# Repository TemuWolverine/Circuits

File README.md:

# Circuits

A collection of PCB designs & KiCad parts that aren't part of larger projects.

### [KicadCustomParts](https://github.com/TemuWolverine/Circuits/tree/master/KicadCustomParts)
- ESP32-S3-Supermini 
    * footprint
    * symbol

### [SparkleButton](https://github.com/TemuWolverine/Circuits/tree/master/SparkleBoard)
Designed as a WS2812b/"Neopixel" push button. Uses two (linked) tactile momentary switches and a WS2812b pixel. The idea is some push buttons can also act as status lights - think the power button on a console - but most off the shelf push buttons are a fixed LED colour.

Needs 5v (LED), LED signal, switch signal and GND.

3D enclosure to come soon.

### [SparkleBoard](https://github.com/TemuWolverine/Circuits/tree/master/SparkleButton)

WIP, USB-PD decoy/trigger and buck converter to provide two voltages. ie 12v for various parts of a project, and 5v for MCU.

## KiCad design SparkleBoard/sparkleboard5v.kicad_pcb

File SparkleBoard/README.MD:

# SparkleBoard 5v (WIP)
SparkleBoard is a USB-PD power board that provides two power rails - one is user selectable from 12v, 15v, 18v or 20v (if the USB-PD power brick supports it) by using jumpers. The other power rail is 5v for microcontrollers.

Amperage defaults to 2a, can be set to 3.25a by cutting JP1

## 5v  -> 3.3v
5v rail is provided via a buck converter - [AP63205](https://www.diodes.com/part/view/AP63205), an inexpensive fixed voltage buck converter from Diodes.

If you wanted 3.3v, this could be achieved by swapping out the chip for the AP63203, and changing the inductor to 3.9uH (from 4.7uH). The rest of the circuit design remains the same according to the manufacturer.

> Note: the AP63200/AP63201 are not fixed voltage output IC's and require additional circuitry with different values and are **NOT** drop in replacements.

## Datasheets
* [AP63205](https://www.diodes.com/datasheet/download/AP63200-AP63201-AP63203-AP63205.pdf)
* [HUSB238](https://www.hynetek.com/uploadfiles/site/219/news/aabbbbdb-48c9-4a44-a6dc-2c15f53282e6.pdf)

## References
* [Sparkfun Babybuck](https://github.com/sparkfun/Buck_Regulator_AP63203/tree/main) (AP6320***3***)
* [Adafruit HUSB238 breakout board](https://github.com/adafruit/Adafruit-USB-Type-C-Power-Delivery-Dummy-Breakout-PCB/tree/main)

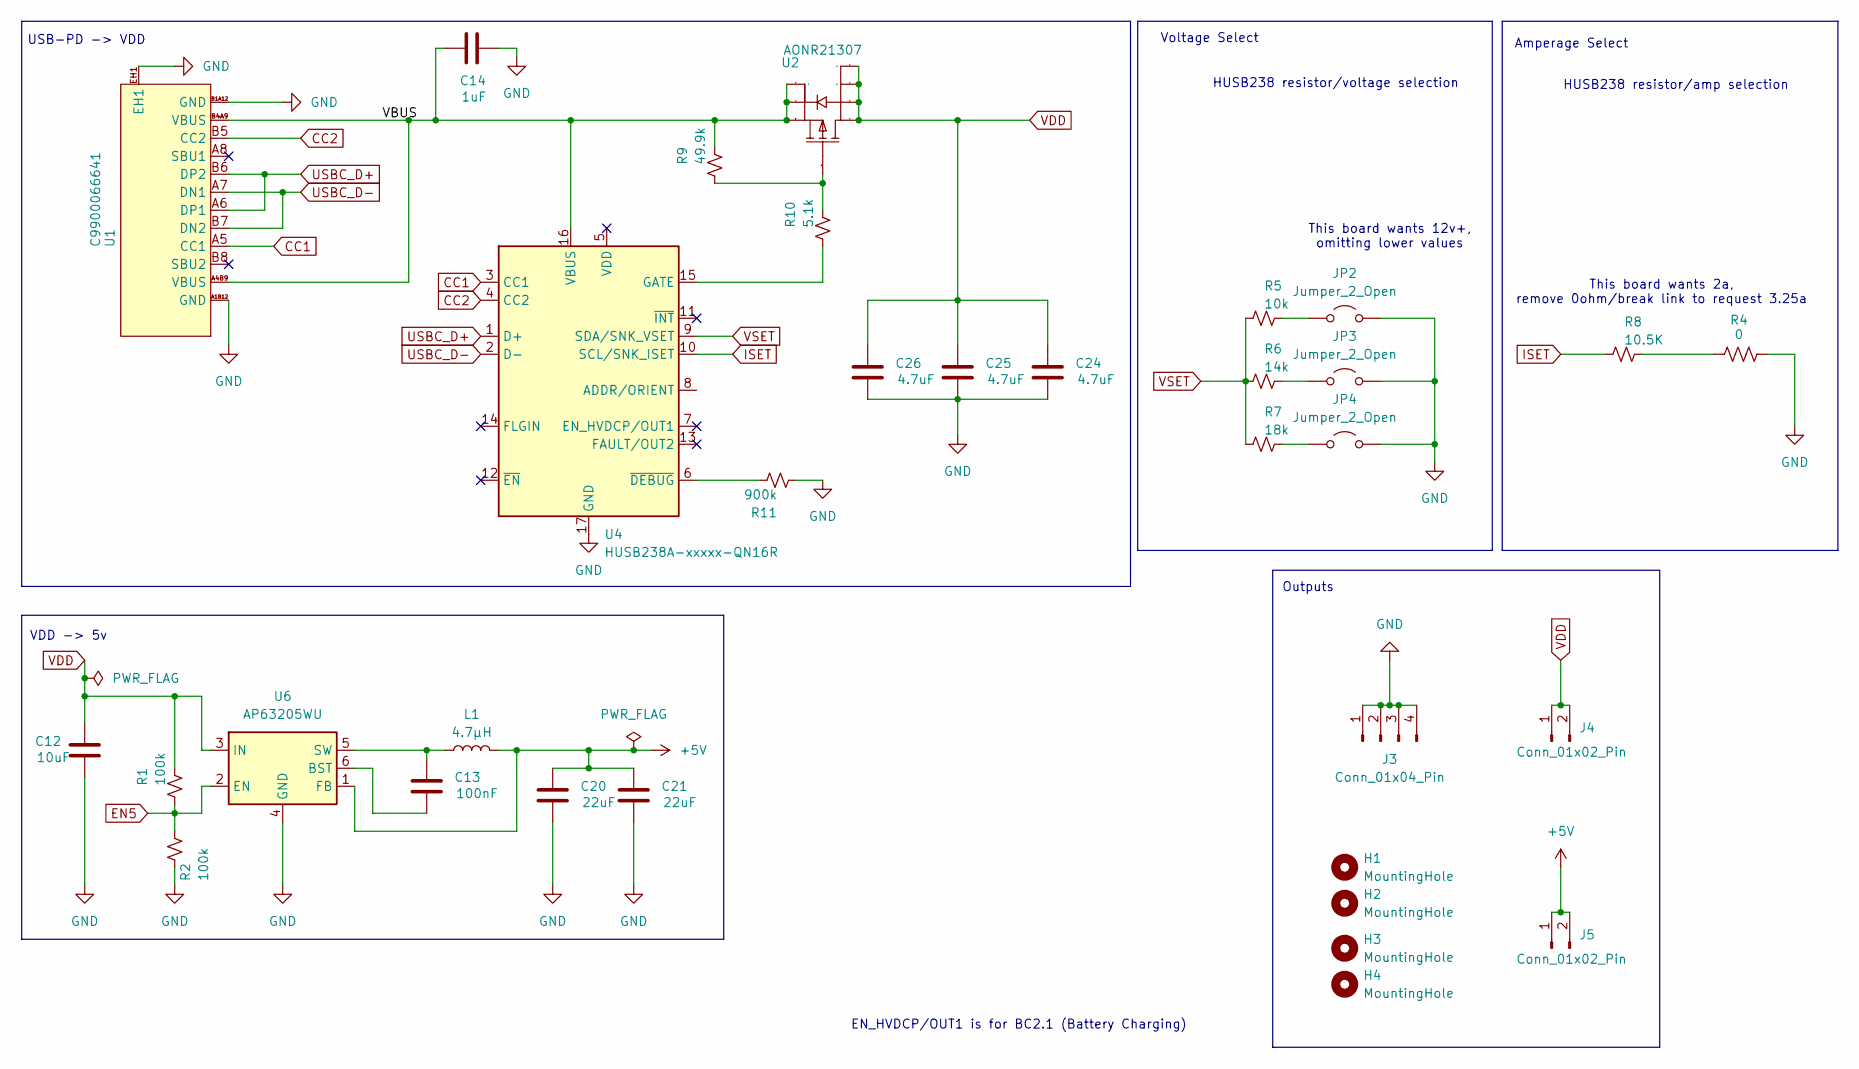
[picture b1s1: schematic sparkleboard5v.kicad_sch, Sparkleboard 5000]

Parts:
C12: 10uF; C_0805_2012Metric
C13: 100nF; C_0805_2012Metric
C14: 1uF; C_0805_2012Metric
C20, C21: 22uF; C_0805_2012Metric
C24, C25, C26: 4.7uF; C_0805_2012Metric
H1, H2, H3, H4: MountingHole; MountingHole_2.7mm_M2.5_DIN965_Pad
J3: Conn_01x04_Pin; CONN-TH_DB125-2.54-4P-GN
J4, J5: Conn_01x02_Pin; PinHeader_1x02_P2.54mm_Vertical
JP2, JP3, JP4: Jumper_2_Open; SolderJumper-2_P1.3mm_Open_TrianglePad1.0x1.5mm
L1: 4.7μH; L_2010_5025Metric
R1, R2: 100k; R_0805_2012Metric
R4: 0; R_0805_2012Metric
R5: 10k; R_0805_2012Metric
R6: 14k; R_0805_2012Metric
R7: 18k; R_0805_2012Metric
R8: 10.5K; R_0805_2012Metric
R9: 49.9k; R_0805_2012Metric
R10: 5.1k; R_0805_2012Metric
R11: 900k; R_0805_2012Metric
U1: C9900066641; TYPE-C-SMD_UC.01.51-11-0017; Manufacturer Part UC.01.51-11-0017,typec; LCSC Part Name UC.01.51-11-0017,typec
U2: AONR21307; PRPAK-8_L3.0-W3.0-P0.65-BL-EP; Manufacturer Part AONR21307; LCSC Part Name 1个P沟道 耐压:30V 电流:24A
U4: HUSB238A-xxxxx-QN16R; WQFN-16-1EP_3x3mm_P0.5mm_EP1.75x1.75mm
U6: AP63205WU; TSOT-23-6

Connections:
+5V: C20.1, C21.1, J5.1, J5.2, L1.2, U6.1 (FB)
/VBUS: C14.2, R9.2, U1.A4B9 (VBUS), U1.B4A9 (VBUS), U2.1 (S), U2.2 (S), U2.3 (S), U4.16 (VBUS)
CC1: U1.A5 (CC1), U4.3 (CC1)
CC2: U1.B5 (CC2), U4.4 (CC2)
EN5: R1.1, R2.2, U6.2 (EN)
GND: C12.2, C14.1, C20.2, C21.2, C24.2, C25.2, C26.2, J3.1, J3.2, J3.3, J3.4, JP2.2 (B), JP3.2 (B), JP4.2 (B), R2.1, R4.1, R11.1, U1.A1B12 (GND), U1.B1A12 (GND), U1.EH1, U4.17 (GND), U6.4 (GND)
ISET: R8.1, U4.10 (SCL/SNK_ISET)
unnamed: JP2.1 (A), R5.2
unnamed: JP3.1 (A), R6.2
unnamed: JP4.1 (A), R7.2
unnamed: R4.2, R8.2
unnamed: R9.1, R10.2, U2.4 (G)
unnamed: R10.1, U4.15 (GATE)
unnamed: R11.2, U4.6 (~DEBUG)
unnamed: C13.2, U6.6 (BST)
unnamed: C13.1, L1.1, U6.5 (SW)
USBC_D+: U1.A6 (DP1), U1.B6 (DP2), U4.1 (D+)
USBC_D-: U1.A7 (DN1), U1.B7 (DN2), U4.2 (D-)
VDD: C12.1, C24.1, C25.1, C26.1, J4.1, J4.2, R1.2, U2.5 (D), U2.6 (D), U2.7 (D), U2.8 (D), U6.3 (IN)
VSET: R5.1, R6.1, R7.1, U4.9 (SDA/SNK_VSET)

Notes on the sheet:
This board wants 12v+, omitting lower values
Outputs
USB-PD -> VDD
HUSB238 resistor/voltage selection
This board wants 2a, remove 0ohm/break link to request 3.25a
VDD -> 5v
Amperage Select
HUSB238 resistor/amp selection
EN_HVDCP/OUT1 is for BC2.1 (Battery Charging)
Voltage Select

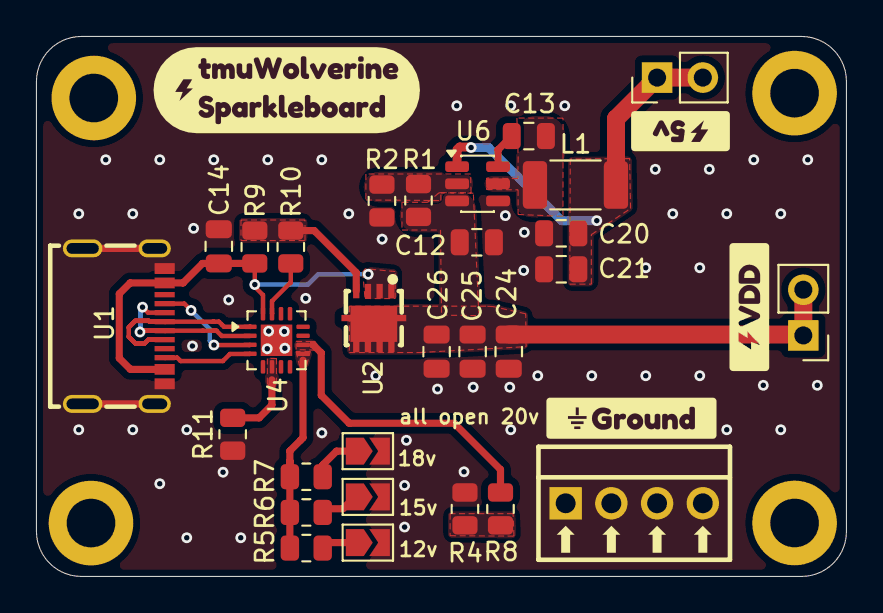
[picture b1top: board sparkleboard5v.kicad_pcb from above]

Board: 2 copper layers, 45.0 x 30.0 mm, 37 parts (0 on the bottom side), 20 nets.

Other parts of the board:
kobee-studio-6A9D10D7, kobee-studio-6A9D10E5, kobee-studio-6A9D10F2: Kobee Studio; kobee-studio-6A9D10A2
kobee-studio-6A969DA9: Kobee Studio; kobee-studio-6A969D7E

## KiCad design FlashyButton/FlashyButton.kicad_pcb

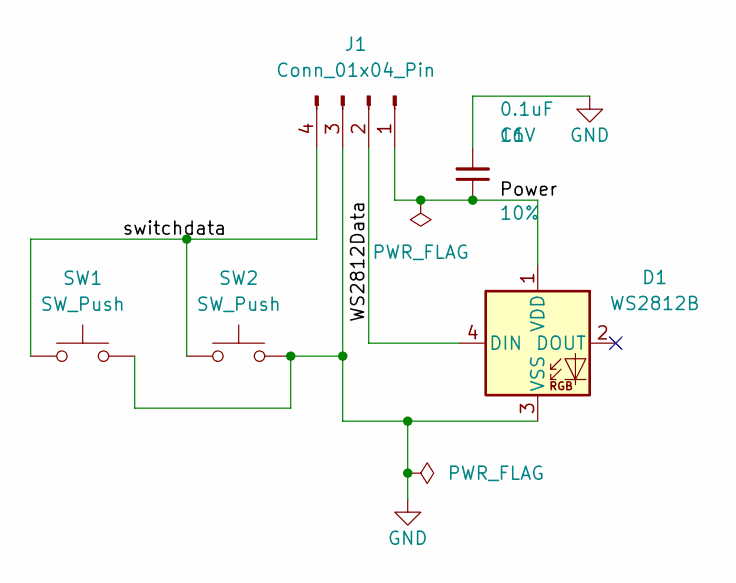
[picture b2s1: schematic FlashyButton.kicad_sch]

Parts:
C1: 0.1uF; C_1206_3216Metric; Voltage 16V; Tolerance 10%
D1: WS2812B; LED_WS2812B_PLCC4_5.0x5.0mm_P3.2mm
J1: Conn_01x04_Pin; PinSocket_1x04_P2.54mm_Vertical
SW1, SW2: SW_Push; SW_PUSH_6mm_H5mm

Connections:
/Power: C1.1, D1.1 (VDD), J1.1
/WS2812Data: D1.4 (DIN), J1.2
/switchdata: J1.4, SW1.1, SW2.1
GND: C1.2, D1.3 (VSS), J1.3, SW1.2, SW2.2

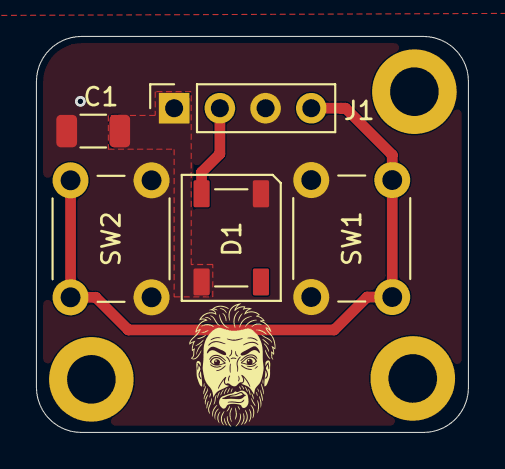
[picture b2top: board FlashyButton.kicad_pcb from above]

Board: 2 copper layers, 24.0 x 22.0 mm, 6 parts (1 on the bottom side), 4 nets.

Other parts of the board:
kibuzzard-6A4DF7DC: G***; kibuzzard-6A4DF7DC
